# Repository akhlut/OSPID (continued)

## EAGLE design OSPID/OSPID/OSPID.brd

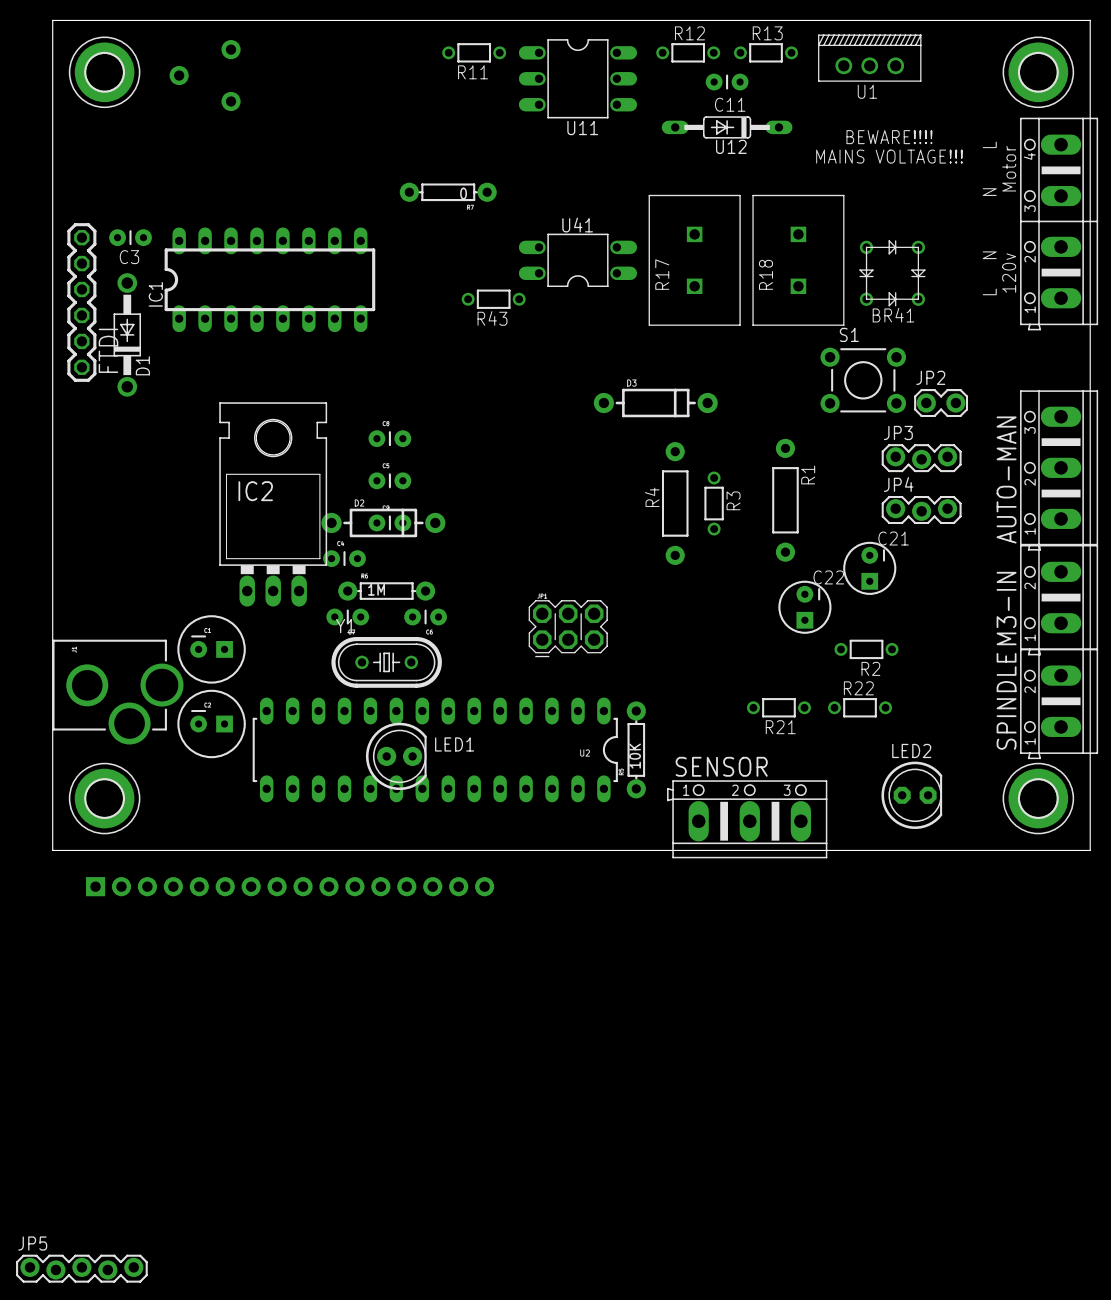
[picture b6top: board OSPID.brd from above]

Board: 2 copper layers, 101.6 x 81.3 mm, 60 parts (0 on the bottom side), 50 nets, no tracks yet.

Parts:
AUTO-MAN: AK500/3
BR41: 2W01G; DIODEBRIDGE
C1, C2: 47uF; CPOL-RADIAL-100UF-25V
C3, C4, C5, C8, C9: 0.1uF; CAP-PTH-SMALL
C6, C7: 22pF; CAP-PTH-SMALL
C11: 0.22uF; CAP-PTH-SMALL
C21, C22: 47uF; CPOL-RADIAL-10UF-25V
D1: 1N4004; DO41-10
D2, D3: DIODE-1N4001
FTDI: FTDI; 6PINHEADER
H5, H6, H7, H8: MOUNT-PAD-ROUND3.6; 3,6-PAD
IC1: 74LS595N; DIL16
IC2: TO-220-ALT
J1: POWER_JACKPTH_LOCK; POWER_JACK_PTH_LOCK
JP1: 2X3_POGO
JP2: 1X02_LOCK
JP3, JP4: 1X03_LOCK
JP5: 1X05_LOCK
LED1, LED2: LED5MM
M3-IN: AK500/2
MAINS1: AK500/4
R1: 4.7k; AXIAL-0.4
R2: 330; 1/6W-RES
R3: 2.2k; 1/6W-RES
R4: 10k; AXIAL-0.4
R5: 10K; AXIAL-0.3
R6: 1M; AXIAL-0.3
R7: 0; AXIAL-0.3
R11: 100; 1/6W-RES
R12: 390; 1/6W-RES
R13: 39; 1/6W-RES
R17: 470; SQM_5-10
R18: 47K; SQM_5-10
R21, R22: 22k; 1/6W-RES
R43: 15k; 1/6W-RES
S1: TACTILE-PTH
SENSOR: AK500/3
SPINDLE: AK500/2
U1: BT139; TRIAC
U2: ATMEGA328P_PDIP; DIL28-3
U3: LCD-16X2NOHOLES; LCD-16X2_NOHOLES
U11: MOC3022M; DIL06
U12: DB3; DO35-10
U41: PC817; DIL04
U$1: TRIM_POT
Y1: 16MHz; HC49U-V

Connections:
!RESET: C3.1, R4.P$2
CS1: JP5.4, U2.6
DTR: C3.2, FTDI.P$6
GND: C1.2, C2.2, C4.2, C5.2, C6.1, C7.2, C8.1, C9.2, C21.2, C22.2, FTDI.P$1, FTDI.P$2, H5.B3,6, H6.B3,6, H7.B3,6, H8.B3,6, IC1.8, IC1.13, IC2.GND, J1.GND, J1.GNDBREAK, JP1.P$6, JP3.3, JP4.3, JP5.5, LED2.K, M3-IN.2, S1.3, S1.4, SENSOR.2, SPINDLE.2, U2.8, U2.22, U3.1, U3.5, U3.16, U11.2, U41.3, U$1.3
MACH3: AUTO-MAN.1, C22.1, R22.2
MACH3_PWM: M3-IN.1, R21.1
MAINS_LIVE: BR41.AC1, C11.1, MAINS1.1, R12.2, U1.2
MANUAL: AUTO-MAN.3, JP4.2
MISO: JP1.P$1, U2.18
MOSI: IC1.14, JP1.P$4, JP5.2, U2.17
MOTOR_LIVE: MAINS1.4, R13.1, U1.3
unnamed: U1.1, U12.C
unnamed: C21.1, R21.2, R22.1
unnamed: U11.4, U12.A
unnamed: LED2.A, R2.2
unnamed: C11.2, R13.2
unnamed: R17.P1, R18.P2, U41.1
unnamed: BR41.-, LED1.K, U41.2
unnamed: LED1.A, R18.P1
unnamed: JP4.1, R3.1
unnamed: U3.3, U$1.1
unnamed: R1.P$1, SPINDLE.1
unnamed: R11.1, U11.1
unnamed: IC1.1, U3.4
unnamed: R12.1, U11.6
unnamed: IC1.2, U3.6
unnamed: IC1.3, U3.11
unnamed: IC1.4, U3.12
unnamed: D3.A, R5.P$2, S1.1, S1.2, U2.1
unnamed: C7.1, R6.P$1, U2.10, Y1.1
unnamed: R7.P$2, U3.15
unnamed: C6.2, R6.P$2, U2.9, Y1.2
unnamed: IC1.5, U3.13
unnamed: IC1.6, U3.14
unnamed: C2.1, D2.C, IC2.IN
unnamed: D2.A, J1.PWR
unnamed: D1.C, JP2.2
unnamed: C8.2, U2.21
unnamed: BR41.+, R17.P2
NEUTRAL: BR41.AC2, MAINS1.2, MAINS1.3
RX: FTDI.P$4, U2.2
SCK: IC1.11, JP1.P$3, JP5.3, U2.19
SENSOR: SENSOR.1, U2.24
SPEED: AUTO-MAN.2, U2.23
SPINDLE-ON: R1.P$2, U2.27
TRIAC: R11.2, U2.26
TX: FTDI.P$5, U2.3
VCC: C1.1, C4.1, C5.1, C9.1, D3.C, IC1.10, IC1.16, IC2.OUT, JP1.P$2, JP2.1, JP3.1, JP5.1, R2.1, R3.2, R4.P$1, R5.P$1, R7.P$1, R43.2, SENSOR.3, U2.7, U2.20, U3.2, U$1.2
VIN: D1.A, FTDI.P$3
ZEROCROSS: R43.1, U2.4, U41.4

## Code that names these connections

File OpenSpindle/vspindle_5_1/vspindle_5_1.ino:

// TRIAC
int triac_control = 5; // Triac control - pin

//RPM control    
int analogPin = 0; // potentiometer or MACH3 - pin
int analogValue = 0;// value to store reading from pot.
//Power
int powerOn = 4; // Power switch - pin 
int powerIndicator = 1; // indicator GREEN LED -pin
// external On/Off from cnc controller
//Zero Detect    
//int zero_detect = 2; //Zero detect - pin
// when using values in the main routine and IRQ routine must be volatile value
volatile byte zero_bit = LOW; // declare IRQ flag
// HIGH = 1, LOW = 0

// HALL SENSOR 
//int  hallsensor = 3; //- pin
unsigned int rpmcount;
unsigned int rpm;
unsigned long timeold;



//LCD
//LiquidCrystal::LiquidCrystal(rs, enable, d0, d1, d2, d3)
#include <LiquidCrystal.h>
LiquidCrystal lcd(13, 11, 7, 8, 9, 10);
//#include <LiquidCrystalFast.h>
//LiquidCrystalFast lcd(13, 12, 11, 7, 8, 9, 10);


// PID
#include <PID_v1.h>

//Define Variables we'll be connecting to
double Setpoint, Input, Output;

//Define the aggressive and conservative Tuning Parameters
double consKp=0.115, consKi=0.4, consKd=0.005;

//Specify the links and initial tuning parameters
PID myPID(&Input, &Output, &Setpoint, consKp, consKi, consKd, DIRECT);
int kDev = 34; // rpm to analog - exp: max rpm = 22000 , analogmax = 1023 : rpm/analogmax = kDev = 21.5
int aDev = 19; // multiplyer for delay



void setup()  
{
//  Serial.begin(9600);
  //Triac control setup  
  pinMode(triac_control, OUTPUT);  
  digitalWrite(triac_control, 0); // LED off
  //Power switch  
  pinMode(powerIndicator, OUTPUT);
  digitalWrite(powerIndicator, 0); // LED off
  pinMode(powerOn, INPUT);
  digitalWrite(powerOn, 1); // pull up
  //Zero detect  
//  pinMode(zero_detect, INPUT);
  attachInterrupt(0, zero_fun, FALLING);  // interrupt 0 digital pin 2 connected ZeroCross circuit
  // Hall sensor  
//  pinMode(hallsensor, INPUT);
  attachInterrupt(1, rpm_fun, FALLING);  // interrupt 1 digital pin 3 connected hall sensor
  rpmcount = 0;
  rpm = 0;
  timeold = 0; 


  // LCD detect
  lcd.begin(16,2);               // initialize the lcd 
  lcd.home ();                   // go home
  lcd.print("Hello, ARDUINO ");  
  lcd.setCursor ( 0, 1 );        // go to the next line
  lcd.print (" vSpindle-2.0   ");    
  delay(3000);
  lcd.clear();  

  //PID

  Input = rpm;
  Setpoint = analogValue;

  //turn the PID on
  myPID.SetMode(AUTOMATIC);
  myPID.SetOutputLimits(79, 511);  
  myPID.SetSampleTime (100);                                





}

void loop() 
{
  //Power switch and indicator = ON/OFF  
  if (!digitalRead(powerOn)) 
  {
    digitalWrite(powerIndicator, 1);        
  }
  else 
  {    
    digitalWrite(powerIndicator, 0);
  }
  //RPM counter and show on LCD
  if (rpmcount >= 30)//Update RPM every 20 counts, increase this for better RPM resolution,
    //decrease for faster update
    
  {
 //    rpm = 60000*1000/(micros() - timeold)*rpmcount;
    
       unsigned long time = millis() - timeold;
       float time_in_sec  = (float)time / 1000;
       float impuls_time  = (float)rpmcount / time_in_sec;
       rpm                = (int)impuls_time*60;
       timeold  = millis(); //set time
       Input = rpm;
       rpmcount = 0; //reset
      if (rpm < 10000) 
      { 
       lcd.setCursor ( 0, 0 );
       lcd.print ("RPM:");
       lcd.setCursor ( 4, 0 );
       lcd.print (" ");
       lcd.setCursor ( 5, 0 );
       lcd.print (rpm);
      }
    else
      {     
       lcd.setCursor ( 0, 0 );
       lcd.print ("RPM:");
       lcd.setCursor ( 4, 0 );
       lcd.print (rpm);  
      }
     
      }

    
    
  //PID 

 int analogValue = analogRead(analogPin); // we are reading pot value

  
  
  if (analogValue*kDev <1800)
  {
    Setpoint = 0;
  }
  else
  {
    Setpoint    = analogValue*kDev;  // setpoint converted to rpm
  }
  myPID.Compute();




  //TRIAC delay control      
  if ((zero_bit == 1) && (digitalRead(powerOn)== 0)) // checking zero bit and power on/off from switch or cnc controller
  {
//    myPID.Compute();
    if (Setpoint >1800) // ignore the Outputs lower then 1000, to low for start the motor
    {
      delayMicroseconds(10000-(Output*aDev)); // delay for triac fiering in reverse, we need smaler delay for more power
      digitalWrite(triac_control, 1); //triac on 
      delayMicroseconds(10);          // triac On propogation delay
      digitalWrite(triac_control, 0);  //triac off 
      zero_bit = 0; // clear flag           
    }   
  }
}

void zero_fun() // set bit
{
  zero_bit = 1;
  // if zero detect set bit == 1
} 

void rpm_fun() // rpm sensor interrupt
{
  rpmcount++;
  //Each rotation, this interrupt function is run twice
}
